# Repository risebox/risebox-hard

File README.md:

# risebox-hard
Hardware Plans &amp; Specifications

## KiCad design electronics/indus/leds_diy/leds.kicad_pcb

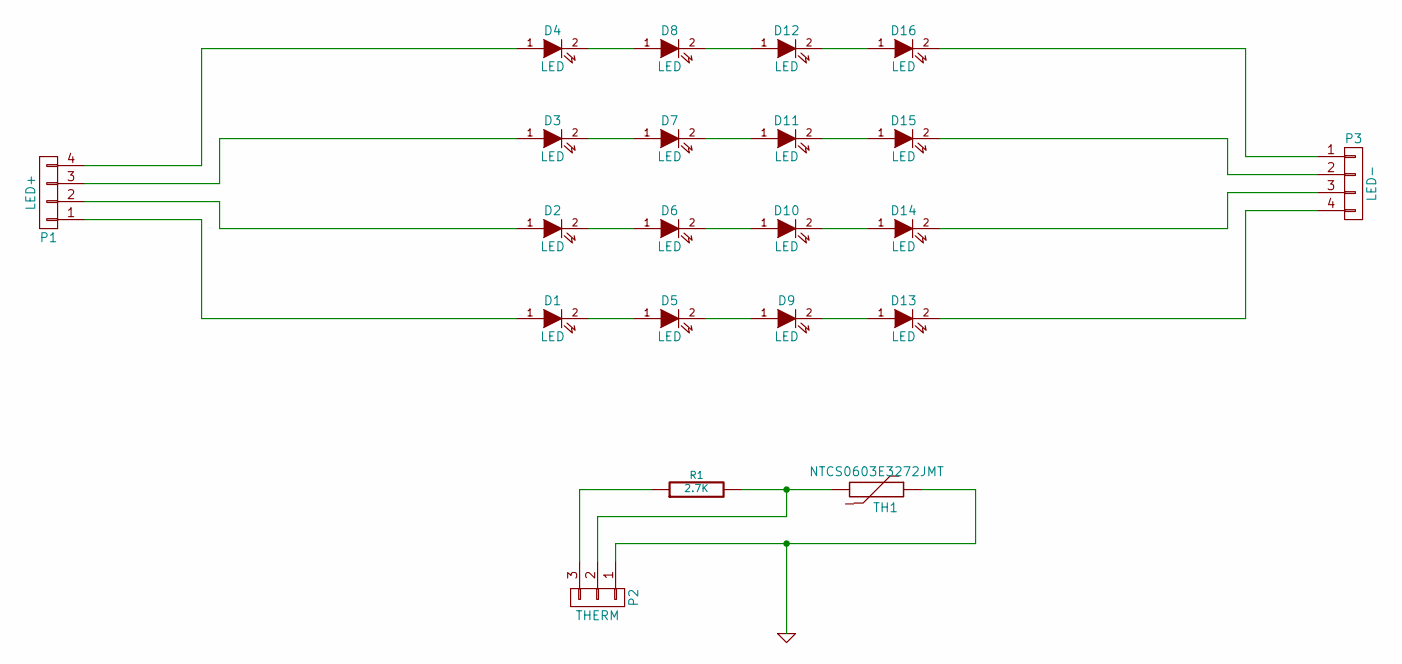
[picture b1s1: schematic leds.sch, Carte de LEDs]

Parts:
D1, D2, D3, D4, D5, D6, D7, D8, D9, D10, D11, D12, D13, D14, D15, D16: LED; LUXEON-C
P1: LED+; CONNECT_TE_3-647166-4
P2: THERM; CONNECT_TE_3-647166-3
P3: LED-; CONNECT_TE_3-647166-4
R1: 2.7K; R_0805
TH1: NTCS0603E3272JMT; THERM_NTCS0603E3272JMT_SMD0603

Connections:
GND: P2.1, TH1.1
unnamed: D1.1 (A), P1.1
unnamed: D1.2 (K), D5.1 (A)
unnamed: D2.1 (A), P1.2
unnamed: D2.2 (K), D6.1 (A)
unnamed: D3.1 (A), P1.3
unnamed: D3.2 (K), D7.1 (A)
unnamed: D4.1 (A), P1.4
unnamed: D4.2 (K), D8.1 (A)
unnamed: D5.2 (K), D9.1 (A)
unnamed: D6.2 (K), D10.1 (A)
unnamed: D10.2 (K), D14.1 (A)
unnamed: D7.2 (K), D11.1 (A)
unnamed: D11.2 (K), D15.1 (A)
unnamed: D8.2 (K), D12.1 (A)
unnamed: D12.2 (K), D16.1 (A)
unnamed: D9.2 (K), D13.1 (A)
unnamed: D13.2 (K), P3.4
unnamed: D14.2 (K), P3.3
unnamed: D15.2 (K), P3.2
unnamed: D16.2 (K), P3.1
unnamed: P2.2, R1.2, TH1.2
unnamed: P2.3, R1.1

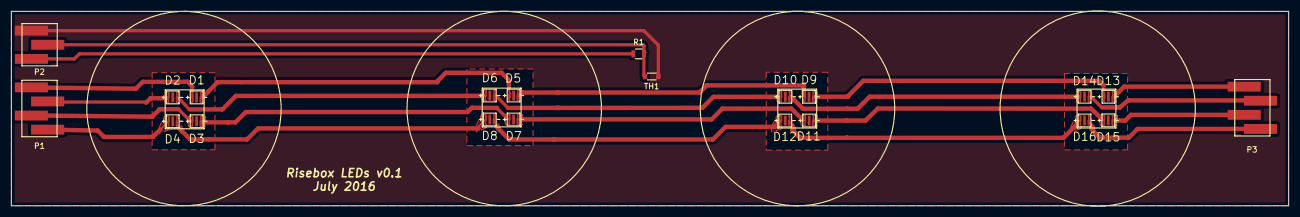
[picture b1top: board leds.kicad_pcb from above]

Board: 2 copper layers, 230.0 x 35.0 mm, 21 parts (0 on the bottom side), 23 nets.

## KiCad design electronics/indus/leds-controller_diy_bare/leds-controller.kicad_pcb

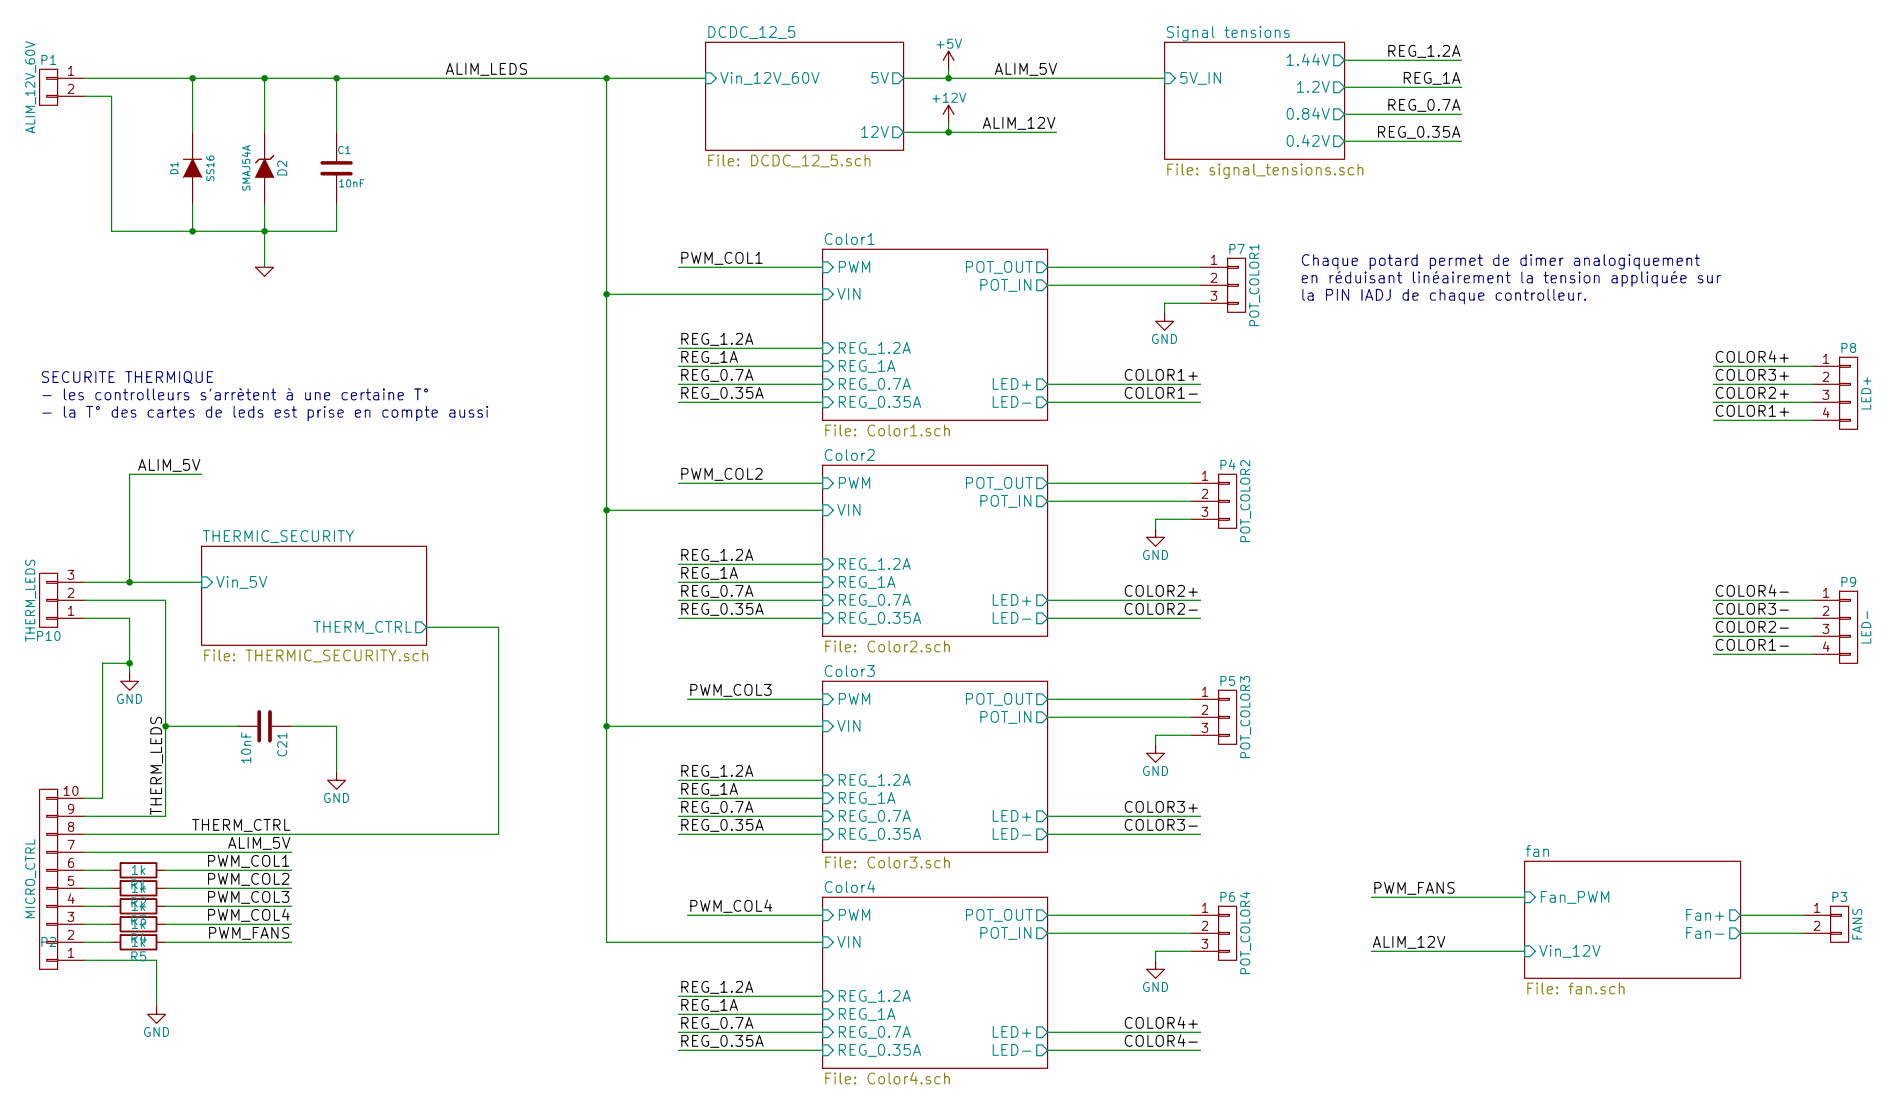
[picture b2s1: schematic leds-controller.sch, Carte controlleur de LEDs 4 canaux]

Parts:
C1, C21: 10nF; C_1206
D1: SS16; AB2_DO-214AC
D2: SMAJ54A; DIODE_DO_214_AA
P1: ALIM_12V_60V; TerminalBlock_Pheonix_MPT-2.54mm_2pol
P2: MICRO_CTRL; PINHEAD_LOCK_1-10
P3: FANS; PINHEAD_LOCK_1-2
P4: POT_COLOR2; POT_PTV09A-4020F-B103
P5: POT_COLOR3; POT_PTV09A-4020F-B103
P6: POT_COLOR4; POT_PTV09A-4020F-B103
P7: POT_COLOR1; POT_PTV09A-4020F-B103
P8: LED+; PINHEAD_LOCK_1-4
P9: LED-; PINHEAD_LOCK_1-4
P10: THERM_LEDS; PINHEAD_LOCK_1-3
R1, R2, R3, R4, R5: 1k; R_0805

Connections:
+5V: P2.7, P10.3; also elsewhere on the board
+12V: P3.1; also elsewhere on the board
/Color1/LED+: P8.4; also elsewhere on the board
/Color1/LED-: P9.4; also elsewhere on the board
/Color1/POT_IN: P7.2; also elsewhere on the board
/Color1/POT_OUT: P7.1; also elsewhere on the board
/Color1/PWM: R1.1; also elsewhere on the board
/Color1/VIN: C1.1, D1.2 (K), D2.2 (K), P1.1; also elsewhere on the board
/Color2/LED+: P8.3; also elsewhere on the board
/Color2/LED-: P9.3; also elsewhere on the board
/Color2/POT_IN: P4.2; also elsewhere on the board
/Color2/POT_OUT: P4.1; also elsewhere on the board
/Color2/PWM: R2.1; also elsewhere on the board
/Color3/LED+: P8.2; also elsewhere on the board
/Color3/LED-: P9.2; also elsewhere on the board
/Color3/POT_IN: P5.2; also elsewhere on the board
/Color3/POT_OUT: P5.1; also elsewhere on the board
/Color3/PWM: R3.1; also elsewhere on the board
/Color4/LED+: P8.1; also elsewhere on the board
/Color4/LED-: P9.1; also elsewhere on the board
/Color4/POT_IN: P6.2; also elsewhere on the board
/Color4/POT_OUT: P6.1; also elsewhere on the board
/Color4/PWM: R4.1; also elsewhere on the board
/THERMIC_SECURITY/THERM_CTRL: P2.8; also elsewhere on the board
/THERM_LEDS: C21.2, P2.9, P10.2
/fan/Fan-: P3.2; also elsewhere on the board
/fan/Fan_PWM: R5.1; also elsewhere on the board
GND: C1.2, C21.1, D1.1 (A), D2.1 (A), P1.2, P2.1, P2.10, P4.3, P5.3, P6.3, P7.3, P10.1; also elsewhere on the board
unnamed: P2.2, R5.2
unnamed: P2.3, R4.2
unnamed: P2.4, R3.2
unnamed: P2.5, R2.2
unnamed: P2.6, R1.2

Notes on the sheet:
Chaque potard permet de dimer analogiquement en réduisant linéairement la tension appliquée sur la PIN IADJ de chaque controlleur.
SECURITE THERMIQUE - les controlleurs s'arrètent à une certaine T° - la T° des cartes de leds est prise en compte aussi

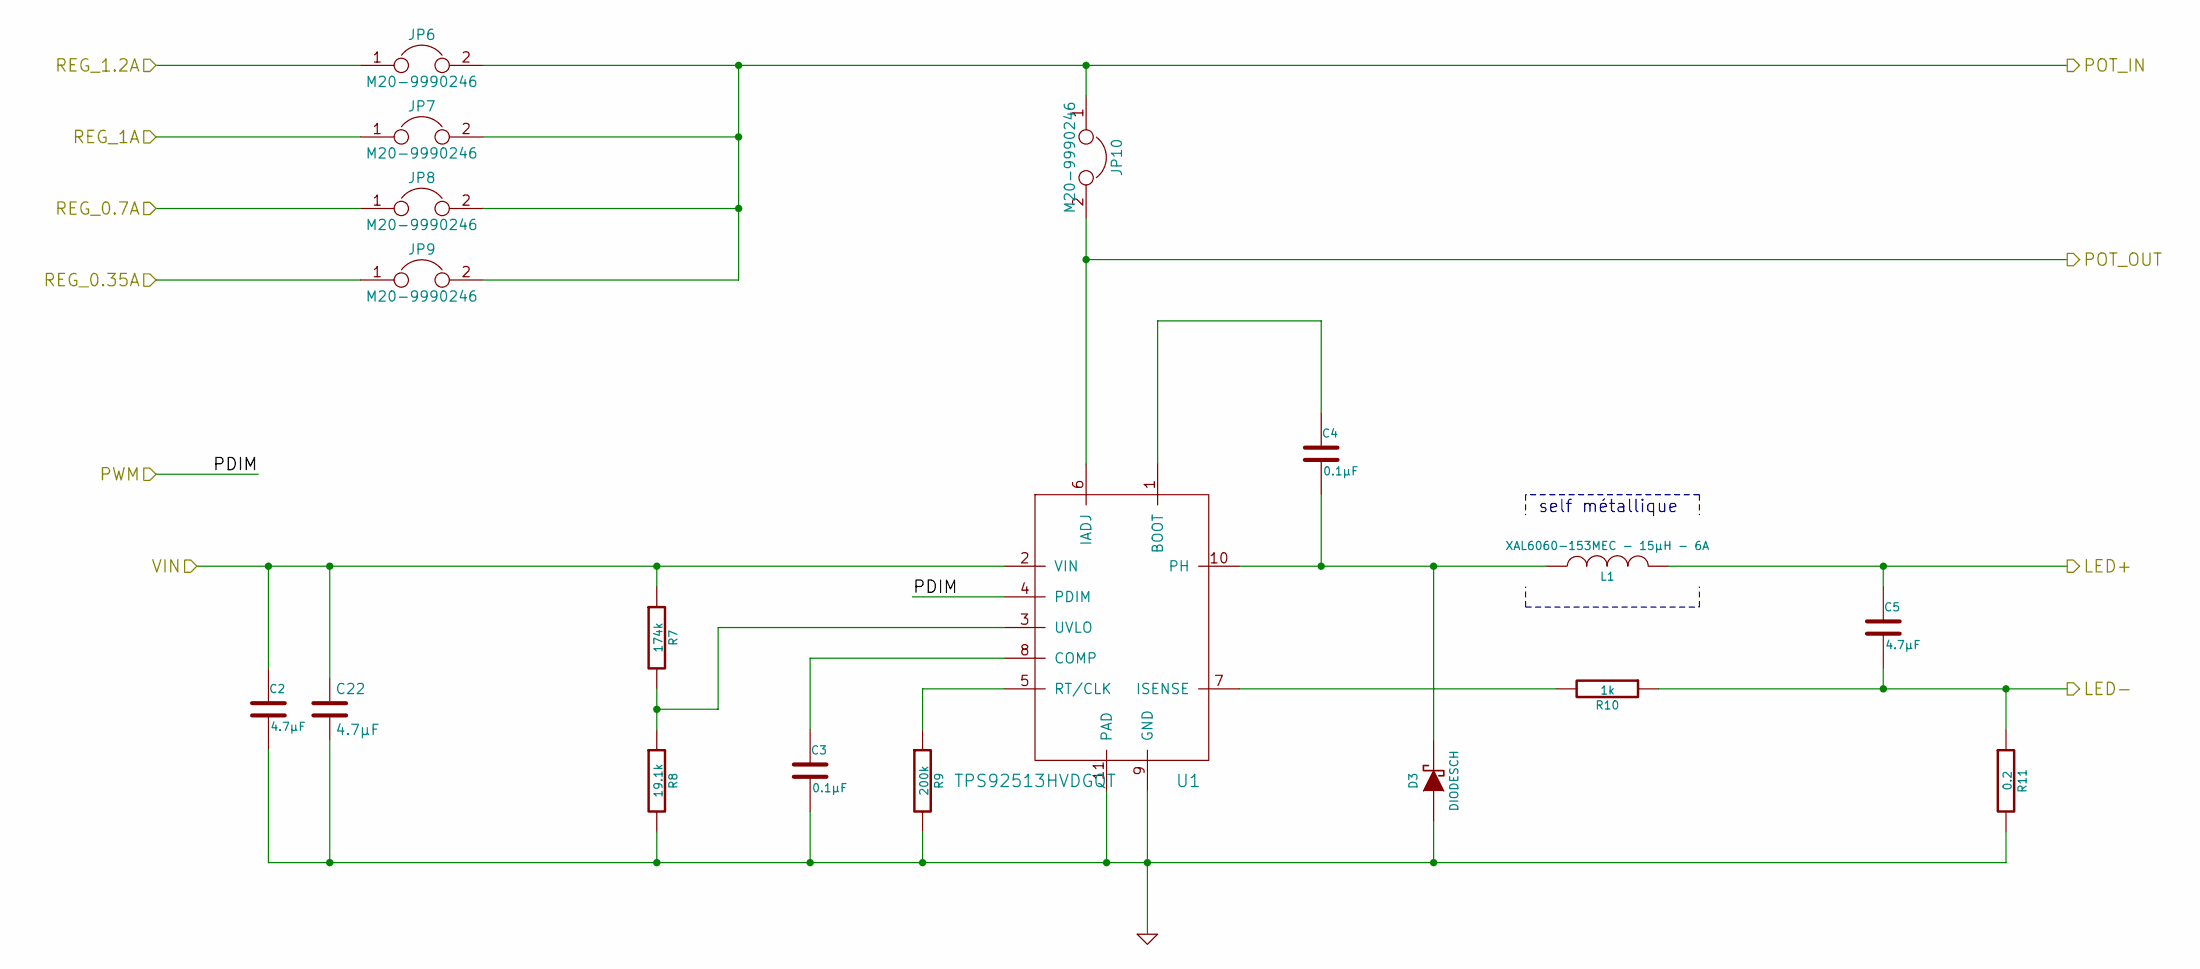
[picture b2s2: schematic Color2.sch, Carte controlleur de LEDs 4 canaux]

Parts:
C2, C5, C22: 4.7µF; C_1206
C3, C4: 0.1µF; C_0805
D3: DIODESCH; SOD-123
JP6, JP7, JP8, JP9, JP10: M20-9990246; PINHEAD1-2
L1: XAL6060-153MEC - 15µH - 6A; SELF_COILCRAFT_XAL6060-153
R7: 174k; R_0805
R8: 19.1k; R_0805
R9: 200k; R_0805
R10: 1k; R_0805
R11: 0.2; R_1206
U1: TPS92513HVDGQT; BUCK_TPS92513_PowerPAD

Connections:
/Color1/VIN: C2.1, C22.1, R7.1, U1.2 (VIN); also elsewhere on the board
/Color2/LED+: C5.1, L1.2; also elsewhere on the board
/Color2/LED-: C5.2, R10.1, R11.1; also elsewhere on the board
/Color2/POT_IN: JP6.2, JP7.2, JP8.2, JP9.2, JP10.1; also elsewhere on the board
/Color2/POT_OUT: JP10.2, U1.6 (IADJ); also elsewhere on the board
/Color2/PWM: U1.4 (PDIM); also elsewhere on the board
/Signal tensions/0.42V: JP9.1; also elsewhere on the board
/Signal tensions/0.84V: JP8.1; also elsewhere on the board
/Signal tensions/1.2V: JP7.1; also elsewhere on the board
/Signal tensions/1.44V: JP6.1; also elsewhere on the board
GND: C2.2, C3.2, C22.2, D3.1 (A), R8.2, R9.2, R11.2, U1.9 (GND), U1.11 (PAD); also elsewhere on the board
unnamed: C3.1, U1.8 (COMP)
unnamed: C4.1, U1.1 (BOOT)
unnamed: C4.2, D3.2 (K), L1.1, U1.10 (PH)
unnamed: R7.2, R8.1, U1.3 (UVLO)
unnamed: R9.1, U1.5 (RT/CLK)
unnamed: R10.2, U1.7 (ISENSE)

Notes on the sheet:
self métallique

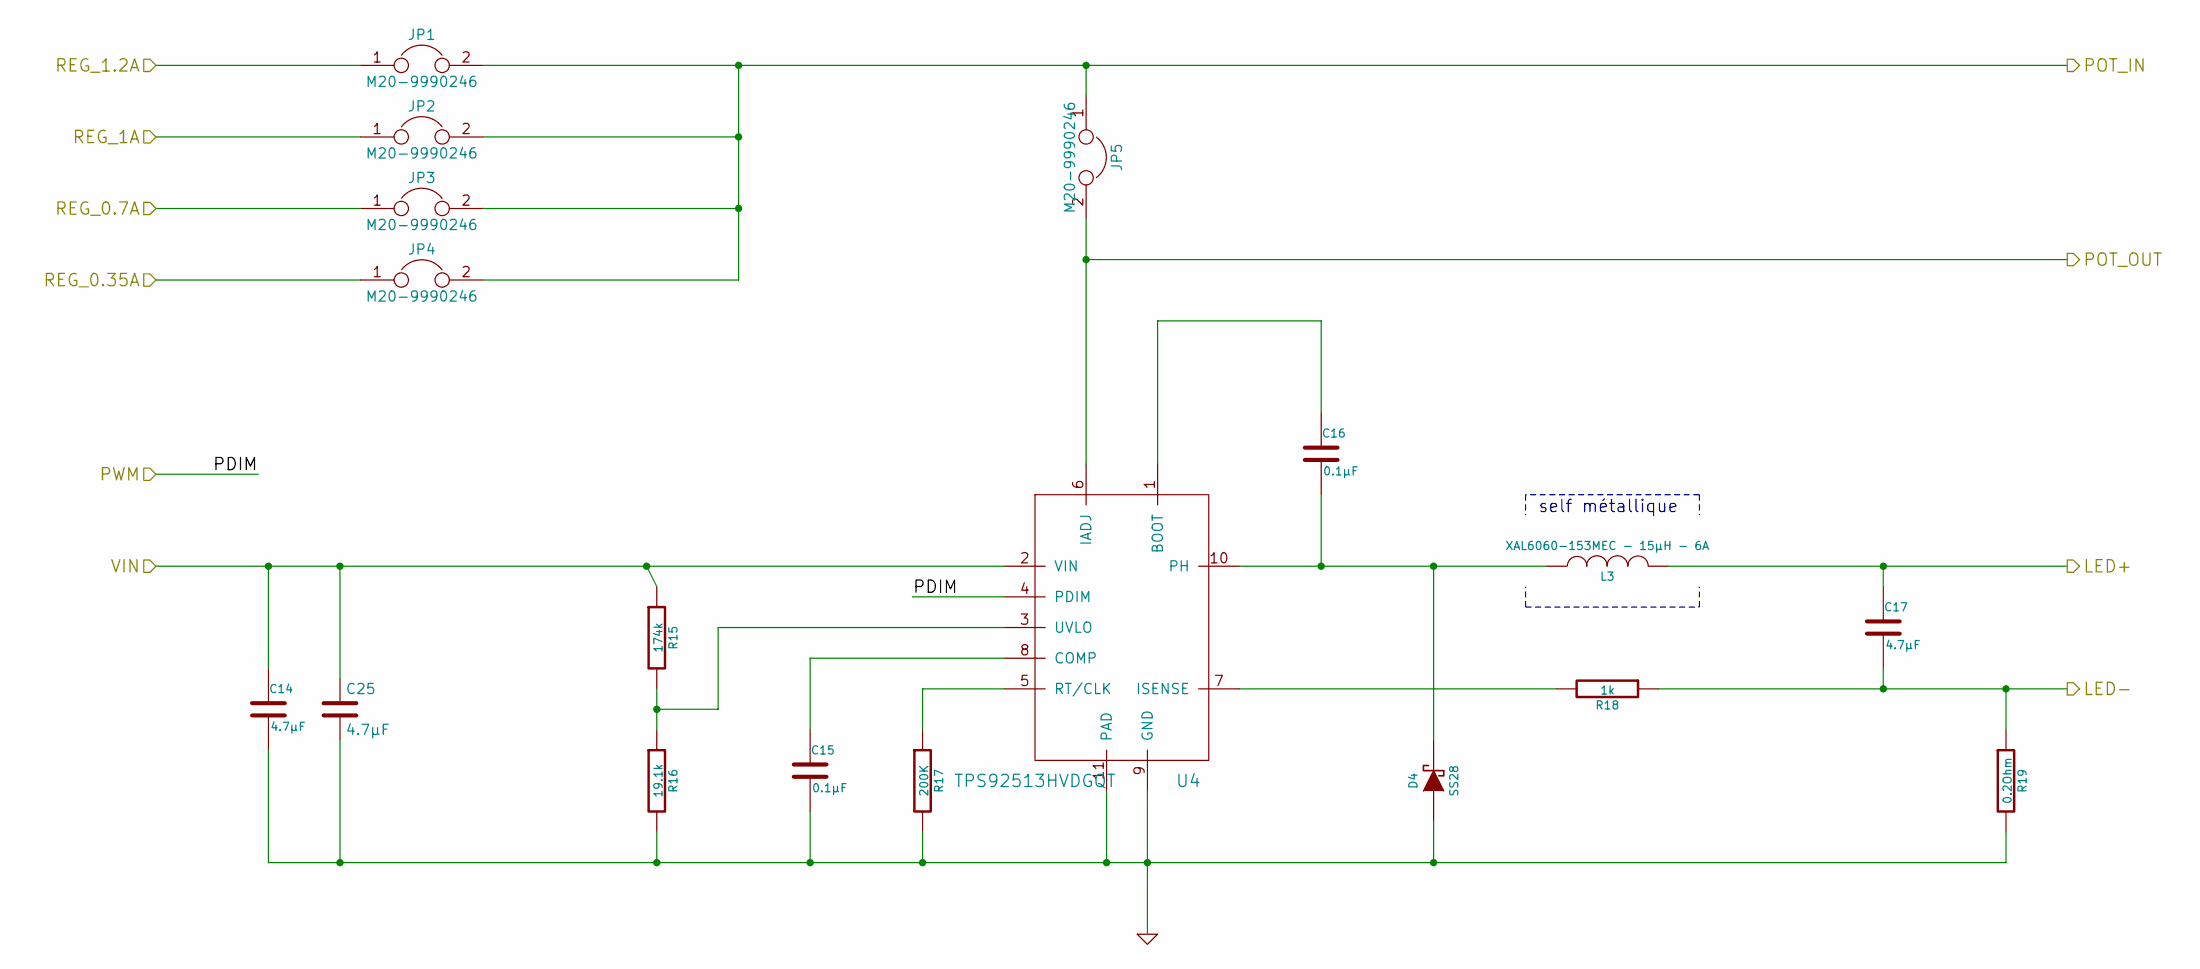
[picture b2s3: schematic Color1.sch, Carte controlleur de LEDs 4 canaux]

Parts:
C14, C17, C25: 4.7µF; C_1206
C15, C16: 0.1µF; C_0805
D4: SS28; SOD-123
JP1, JP2, JP3, JP4, JP5: M20-9990246; PINHEAD1-2
L3: XAL6060-153MEC - 15µH - 6A; SELF_COILCRAFT_XAL6060-153
R15: 174k; R_0805
R16: 19.1k; R_0805
R17: 200K; R_0805
R18: 1k; R_0805
R19: 0.2Ohm; R_1206
U4: TPS92513HVDGQT; BUCK_TPS92513_PowerPAD

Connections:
/Color1/LED+: C17.1, L3.2; also elsewhere on the board
/Color1/LED-: C17.2, R18.1, R19.1; also elsewhere on the board
/Color1/POT_IN: JP1.2, JP2.2, JP3.2, JP4.2, JP5.1; also elsewhere on the board
/Color1/POT_OUT: JP5.2, U4.6 (IADJ); also elsewhere on the board
/Color1/PWM: U4.4 (PDIM); also elsewhere on the board
/Color1/VIN: C14.1, C25.1, R15.1, U4.2 (VIN); also elsewhere on the board
/Signal tensions/0.42V: JP4.1; also elsewhere on the board
/Signal tensions/0.84V: JP3.1; also elsewhere on the board
/Signal tensions/1.2V: JP2.1; also elsewhere on the board
/Signal tensions/1.44V: JP1.1; also elsewhere on the board
GND: C14.2, C15.2, C25.2, D4.1 (A), R16.2, R17.2, R19.2, U4.9 (GND), U4.11 (PAD); also elsewhere on the board
unnamed: C15.1, U4.8 (COMP)
unnamed: C16.1, U4.1 (BOOT)
unnamed: C16.2, D4.2 (K), L3.1, U4.10 (PH)
unnamed: R15.2, R16.1, U4.3 (UVLO)
unnamed: R17.1, U4.5 (RT/CLK)
unnamed: R18.2, U4.7 (ISENSE)

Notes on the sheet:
self métallique

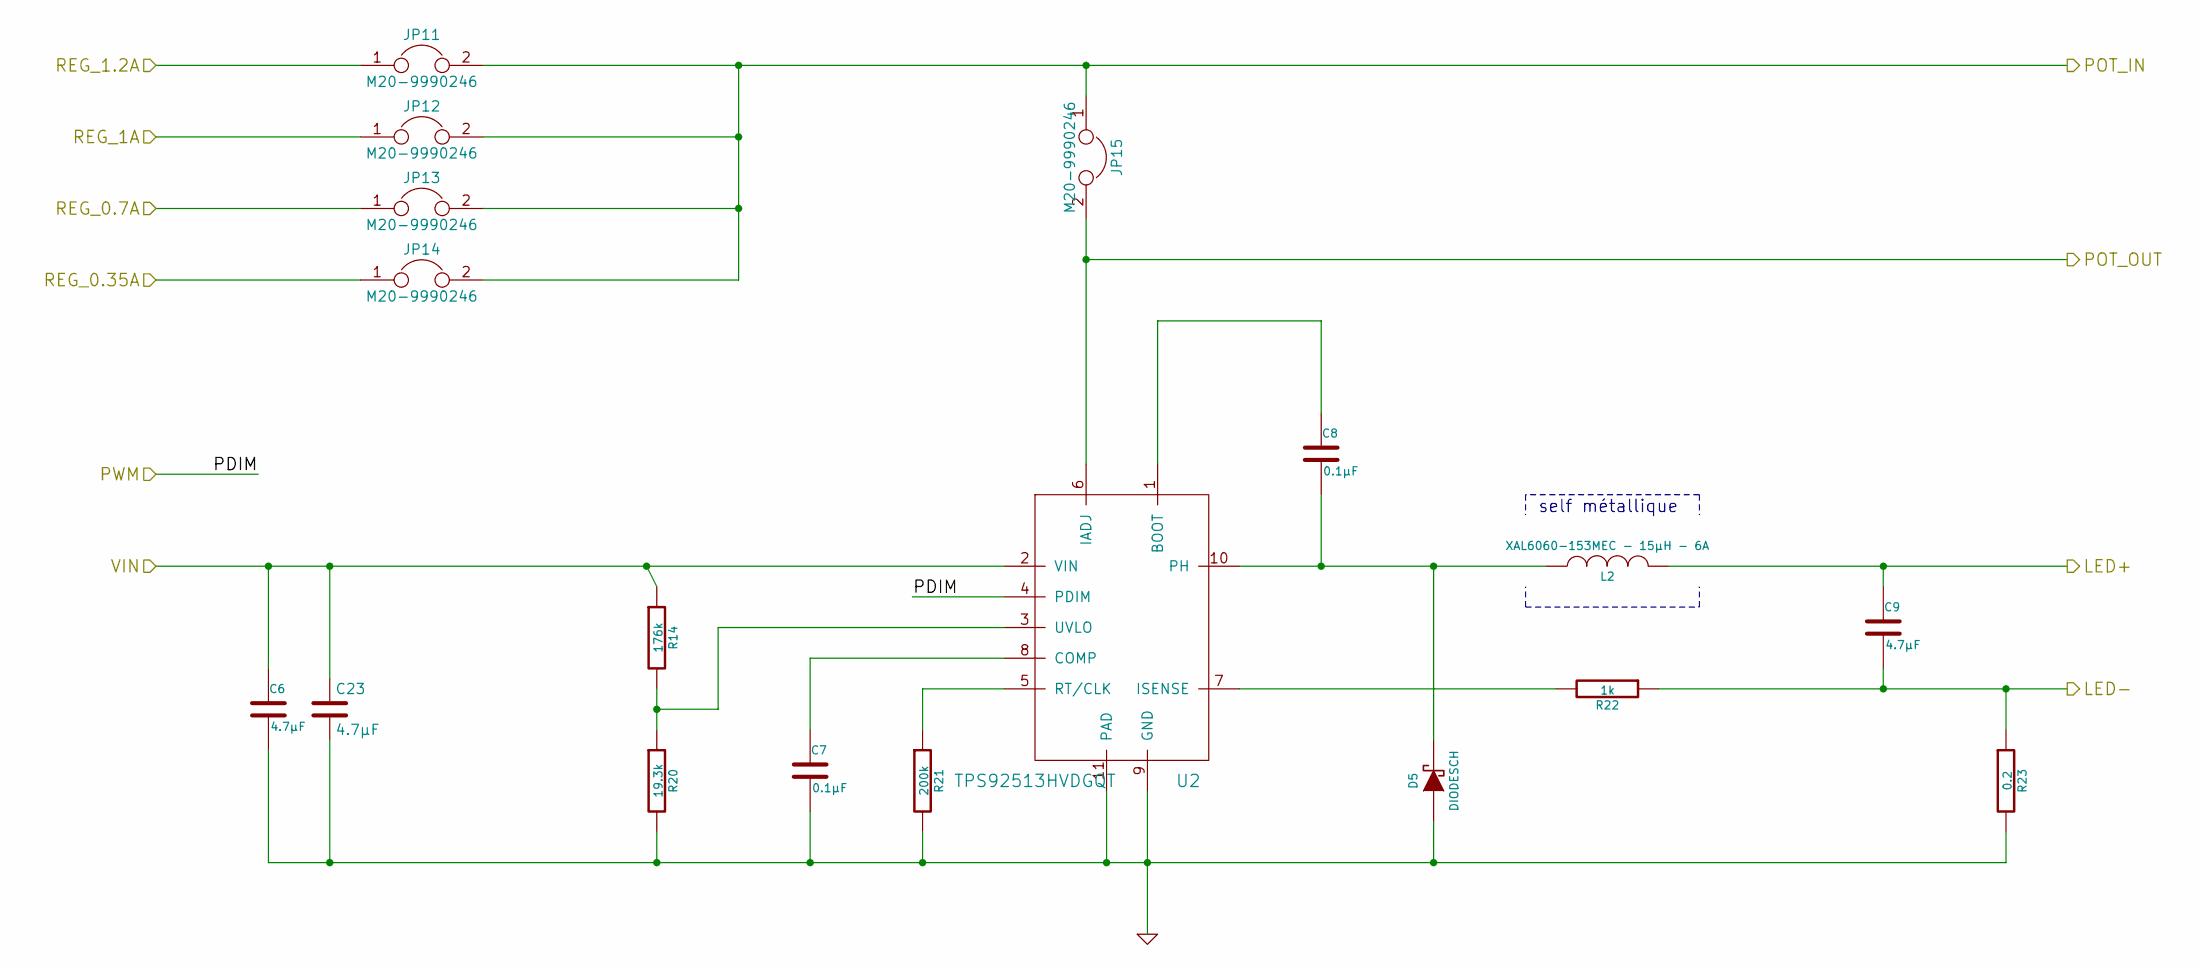
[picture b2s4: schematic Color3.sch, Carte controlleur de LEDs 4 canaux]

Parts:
C6, C9, C23: 4.7µF; C_1206
C7, C8: 0.1µF; C_0805
D5: DIODESCH; SOD-123
JP11, JP12, JP13, JP14, JP15: M20-9990246; PINHEAD1-2
L2: XAL6060-153MEC - 15µH - 6A; SELF_COILCRAFT_XAL6060-153
R14: 176k; R_0805
R20: 19.3k; R_0805
R21: 200k; R_0805
R22: 1k; R_0805
R23: 0.2; R_1206
U2: TPS92513HVDGQT; BUCK_TPS92513_PowerPAD

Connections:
/Color1/VIN: C6.1, C23.1, R14.1, U2.2 (VIN); also elsewhere on the board
/Color3/LED+: C9.1, L2.2; also elsewhere on the board
/Color3/LED-: C9.2, R22.1, R23.1; also elsewhere on the board
/Color3/POT_IN: JP11.2, JP12.2, JP13.2, JP14.2, JP15.1; also elsewhere on the board
/Color3/POT_OUT: JP15.2, U2.6 (IADJ); also elsewhere on the board
/Color3/PWM: U2.4 (PDIM); also elsewhere on the board
/Signal tensions/0.42V: JP14.1; also elsewhere on the board
/Signal tensions/0.84V: JP13.1; also elsewhere on the board
/Signal tensions/1.2V: JP12.1; also elsewhere on the board
/Signal tensions/1.44V: JP11.1; also elsewhere on the board
GND: C6.2, C7.2, C23.2, D5.1 (A), R20.2, R21.2, R23.2, U2.9 (GND), U2.11 (PAD); also elsewhere on the board
unnamed: C7.1, U2.8 (COMP)
unnamed: C8.1, U2.1 (BOOT)
unnamed: C8.2, D5.2 (K), L2.1, U2.10 (PH)
unnamed: R14.2, R20.1, U2.3 (UVLO)
unnamed: R21.1, U2.5 (RT/CLK)
unnamed: R22.2, U2.7 (ISENSE)

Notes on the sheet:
self métallique

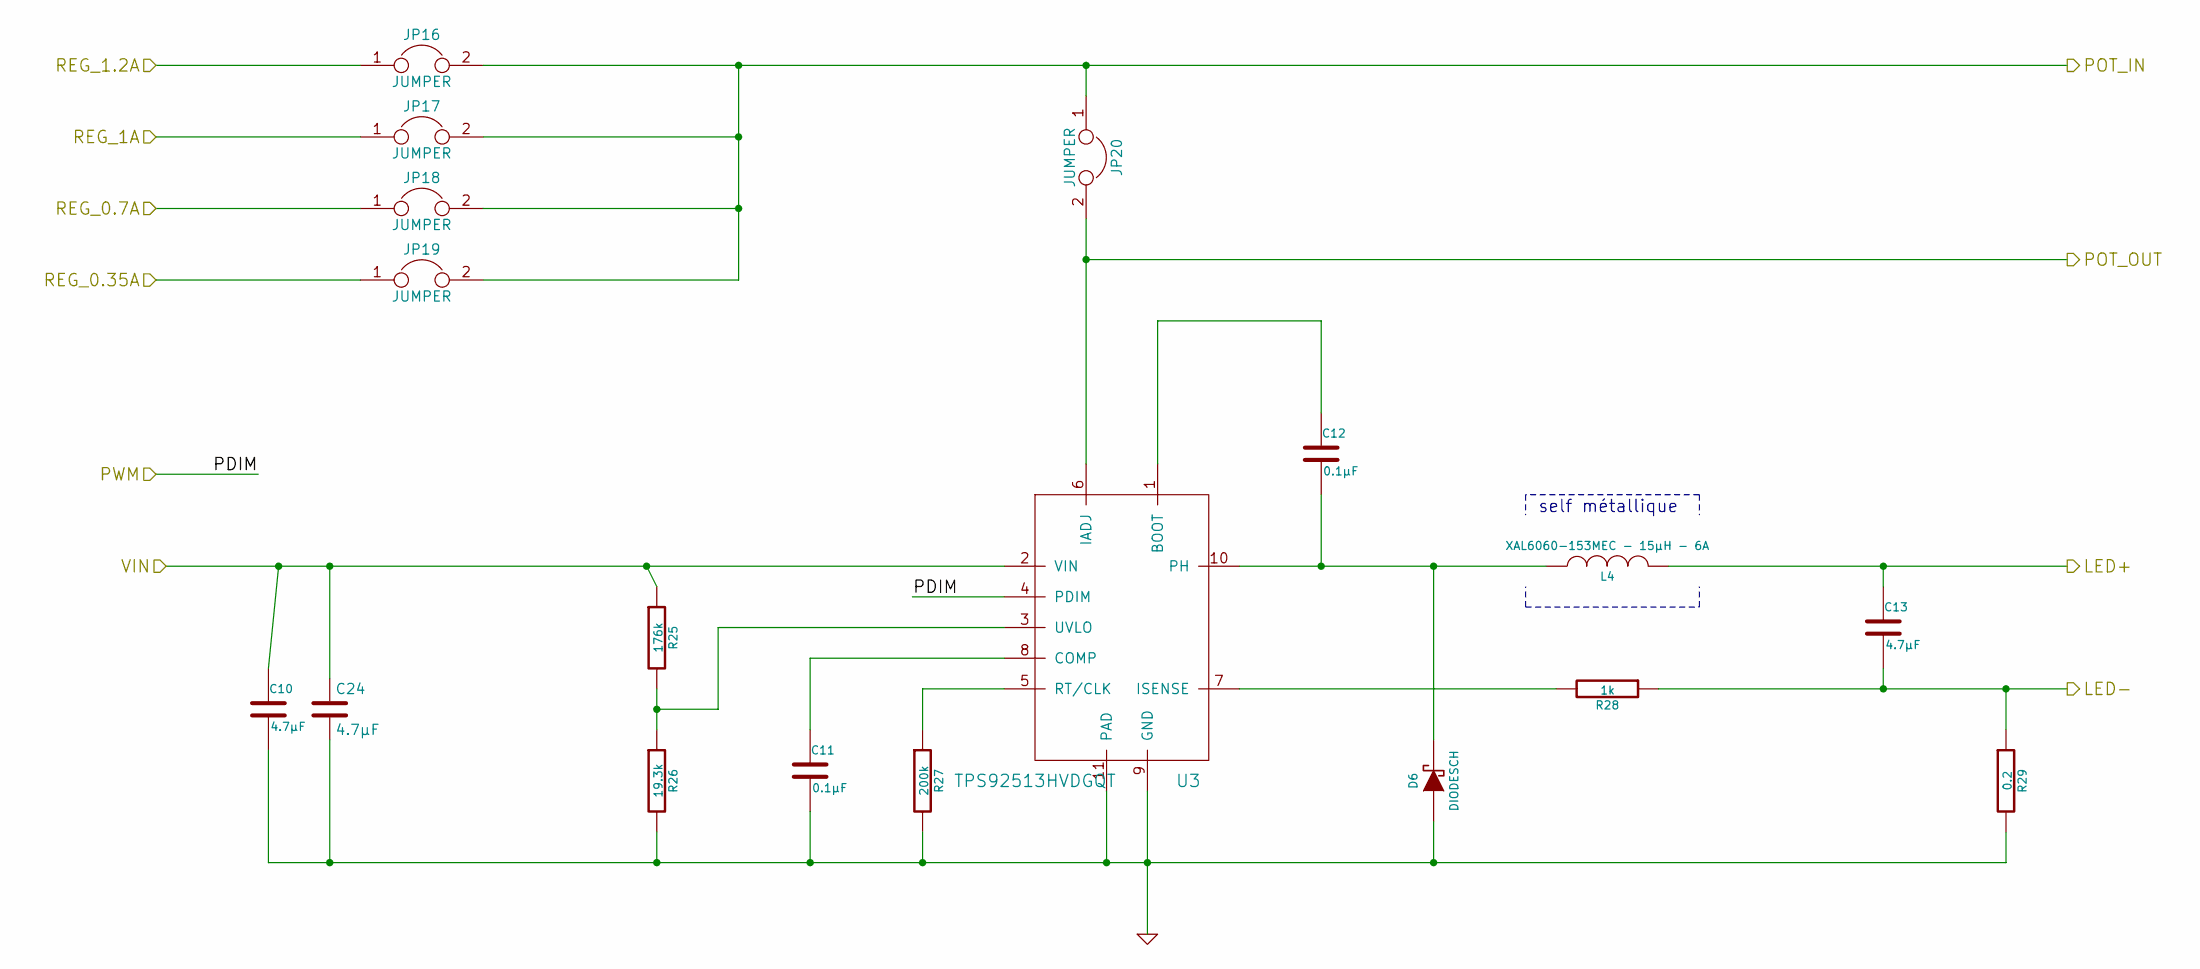
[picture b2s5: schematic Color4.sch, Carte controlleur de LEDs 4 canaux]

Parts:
C10, C13, C24: 4.7µF; C_1206
C11, C12: 0.1µF; C_0805
D6: DIODESCH; SOD-123
JP16, JP17, JP18, JP19, JP20: JUMPER
L4: XAL6060-153MEC - 15µH - 6A; SELF_COILCRAFT_XAL6060-153
R25: 176k; R_0805
R26: 19.3k; R_0805
R27: 200k; R_0805
R28: 1k; R_0805
R29: 0.2; R_1206
U3: TPS92513HVDGQT; BUCK_TPS92513_PowerPAD

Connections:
/Color1/VIN: C10.1, C24.1, R25.1, U3.2 (VIN); also elsewhere on the board
/Color4/LED+: C13.1, L4.2; also elsewhere on the board
/Color4/LED-: C13.2, R28.1, R29.1; also elsewhere on the board
/Color4/POT_IN: JP16.2, JP17.2, JP18.2, JP19.2, JP20.1; also elsewhere on the board
/Color4/POT_OUT: JP20.2, U3.6 (IADJ); also elsewhere on the board
/Color4/PWM: U3.4 (PDIM); also elsewhere on the board
/Signal tensions/0.42V: JP19.1; also elsewhere on the board
/Signal tensions/0.84V: JP18.1; also elsewhere on the board
/Signal tensions/1.2V: JP17.1; also elsewhere on the board
/Signal tensions/1.44V: JP16.1; also elsewhere on the board
GND: C10.2, C11.2, C24.2, D6.1 (A), R26.2, R27.2, R29.2, U3.9 (GND), U3.11 (PAD); also elsewhere on the board
unnamed: C11.1, U3.8 (COMP)
unnamed: C12.1, U3.1 (BOOT)
unnamed: C12.2, D6.2 (K), L4.1, U3.10 (PH)
unnamed: R25.2, R26.1, U3.3 (UVLO)
unnamed: R27.1, U3.5 (RT/CLK)
unnamed: R28.2, U3.7 (ISENSE)

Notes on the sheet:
self métallique

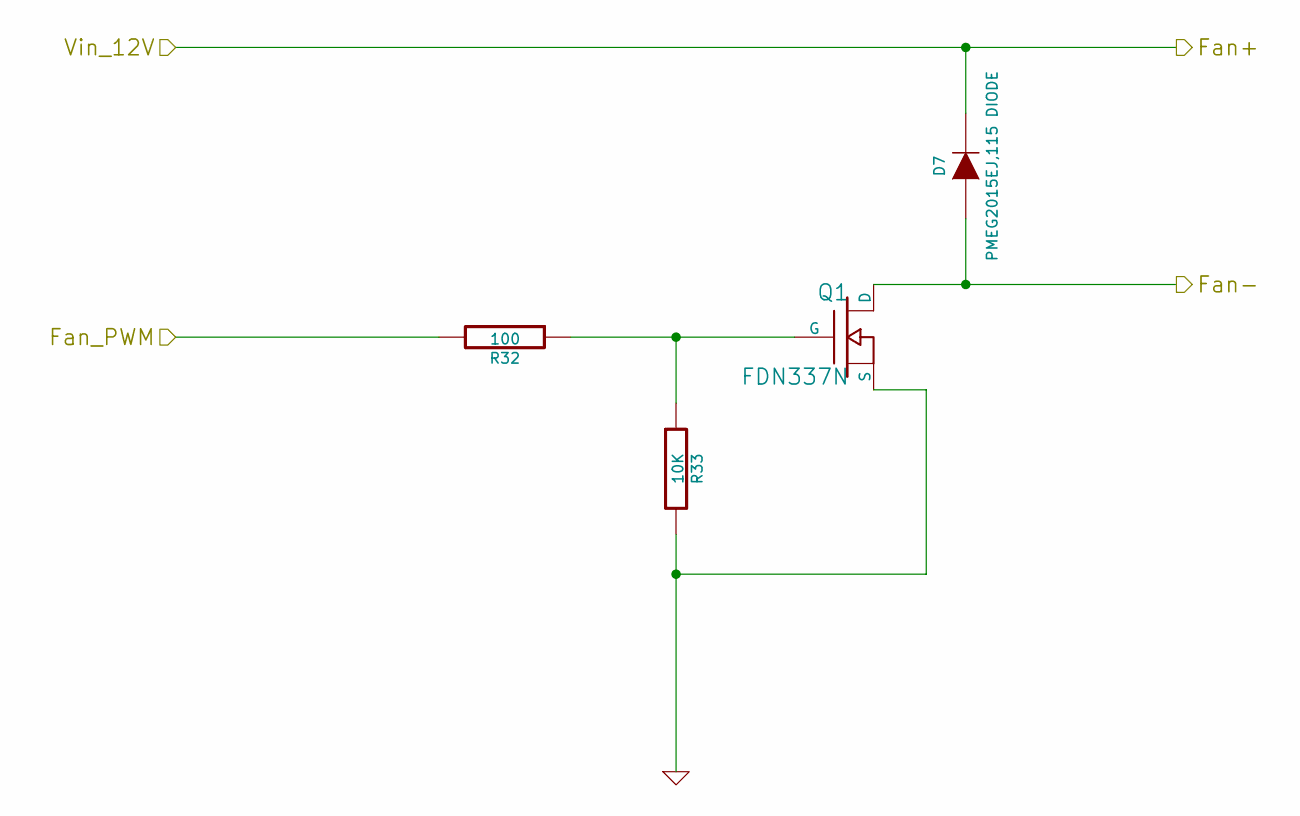
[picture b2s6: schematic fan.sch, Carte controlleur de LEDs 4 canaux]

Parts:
D7: PMEG2015EJ,115 DIODE; AB2_DO-214AC
Q1: FDN337N; SOT-23-FET
R32: 100; R_0603
R33: 10K; R_0603

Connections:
+12V: D7.2 (K); also elsewhere on the board
/fan/Fan-: D7.1 (A), Q1.D; also elsewhere on the board
/fan/Fan_PWM: R32.2; also elsewhere on the board
GND: Q1.S, R33.2; also elsewhere on the board
unnamed: Q1.G, R32.1, R33.1

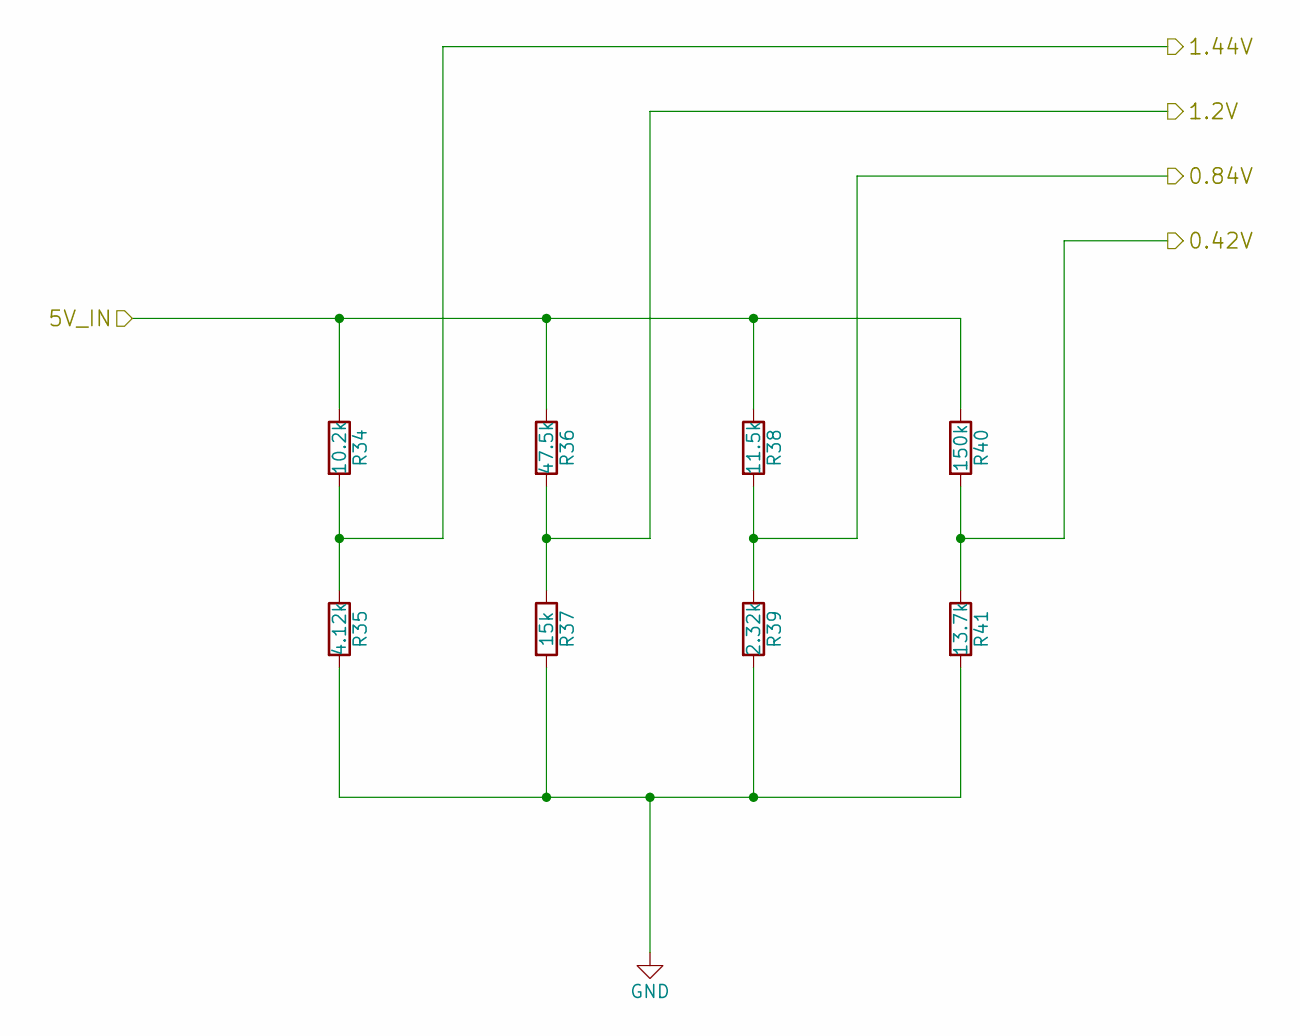
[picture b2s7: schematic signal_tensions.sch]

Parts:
R34: 10.2k; R_0805
R35: 4.12k; R_0805
R36: 47.5k; R_0805
R37: 15k; R_0805
R38: 11.5k; R_0805
R39: 2.32k; R_0805
R40: 150k; R_0805
R41: 13.7k; R_0805

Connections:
+5V: R34.1, R36.1, R38.1, R40.1; also elsewhere on the board
/Signal tensions/0.42V: R40.2, R41.1; also elsewhere on the board
/Signal tensions/0.84V: R38.2, R39.1; also elsewhere on the board
/Signal tensions/1.2V: R36.2, R37.1; also elsewhere on the board
/Signal tensions/1.44V: R34.2, R35.1; also elsewhere on the board
GND: R35.2, R37.2, R39.2, R41.2; also elsewhere on the board

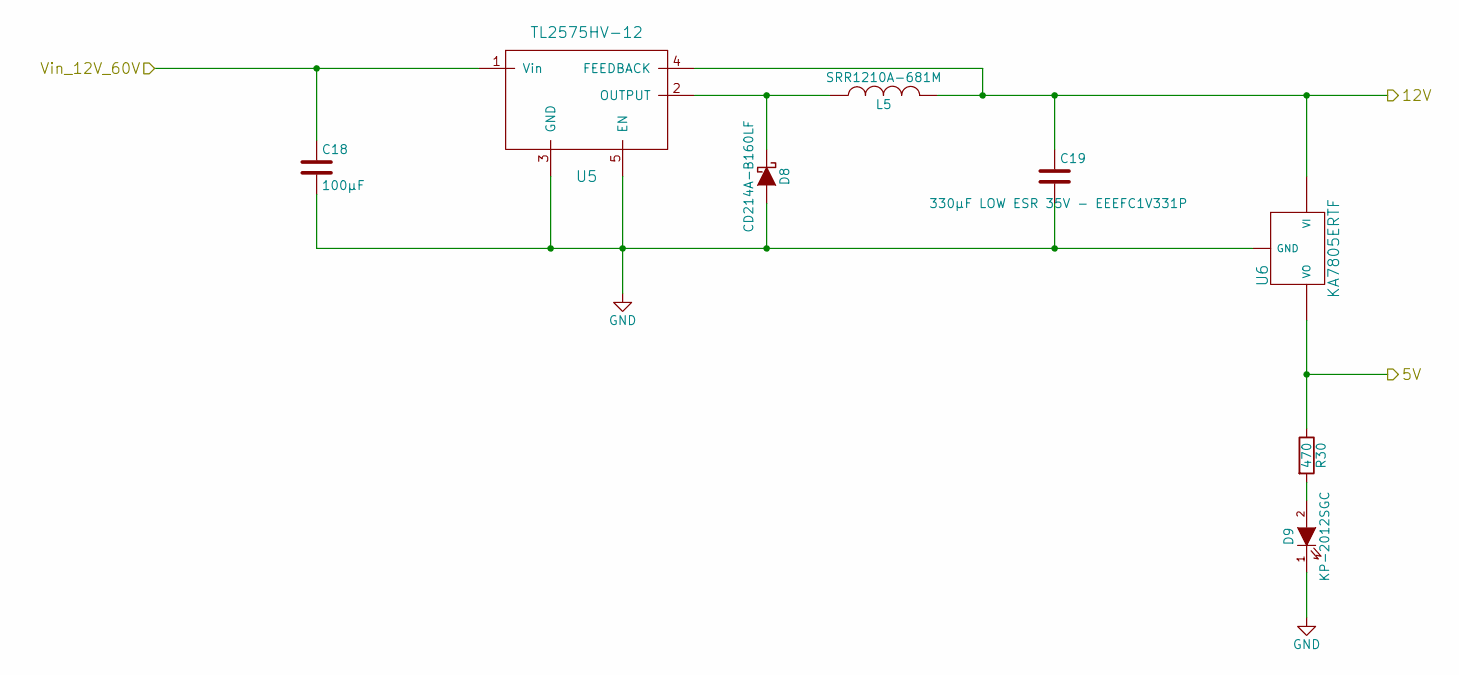
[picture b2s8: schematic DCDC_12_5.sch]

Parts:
C18: 100µF; C_Radial_D10_L20_P5
C19: 330µF LOW ESR 35V - EEEFC1V331P; CAPA_EEEFC1V331P
D8: CD214A-B160LF; AB2_DO-214AC
D9: KP-2012SGC; LED-KPH-2012SGC
L5: SRR1210A-681M; INDUC_SRR1210A
R30: 470; R_0805
U5: TL2575HV-12; TO-263-5Lead
U6: KA7805ERTF; KA7805ERTF_TO-252-3

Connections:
+5V: R30.1, U6.VO; also elsewhere on the board
+12V: C19.1, L5.2, U5.4 (FEEDBACK), U6.VI; also elsewhere on the board
/Color1/VIN: C18.1, U5.1 (Vin); also elsewhere on the board
GND: C18.2, C19.2, D8.2 (A), D9.1 (K), U5.3 (GND), U5.5 (EN), U6.GND; also elsewhere on the board
unnamed: D8.1 (K), L5.1, U5.2 (OUTPUT)
unnamed: D9.2 (A), R30.2

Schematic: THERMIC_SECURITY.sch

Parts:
C20: 10nF; C_1206
R42: 2.55K; R_0805
TH1: NTCS0805E3103JMT; THERM_NTCS0603E3272JMT_SMD0603

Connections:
+5V: TH1.1; also elsewhere on the board
/THERMIC_SECURITY/THERM_CTRL: C20.1, R42.1, TH1.2; also elsewhere on the board
GND: C20.2, R42.2; also elsewhere on the board

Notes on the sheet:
1V à 25°, 4V à 115°

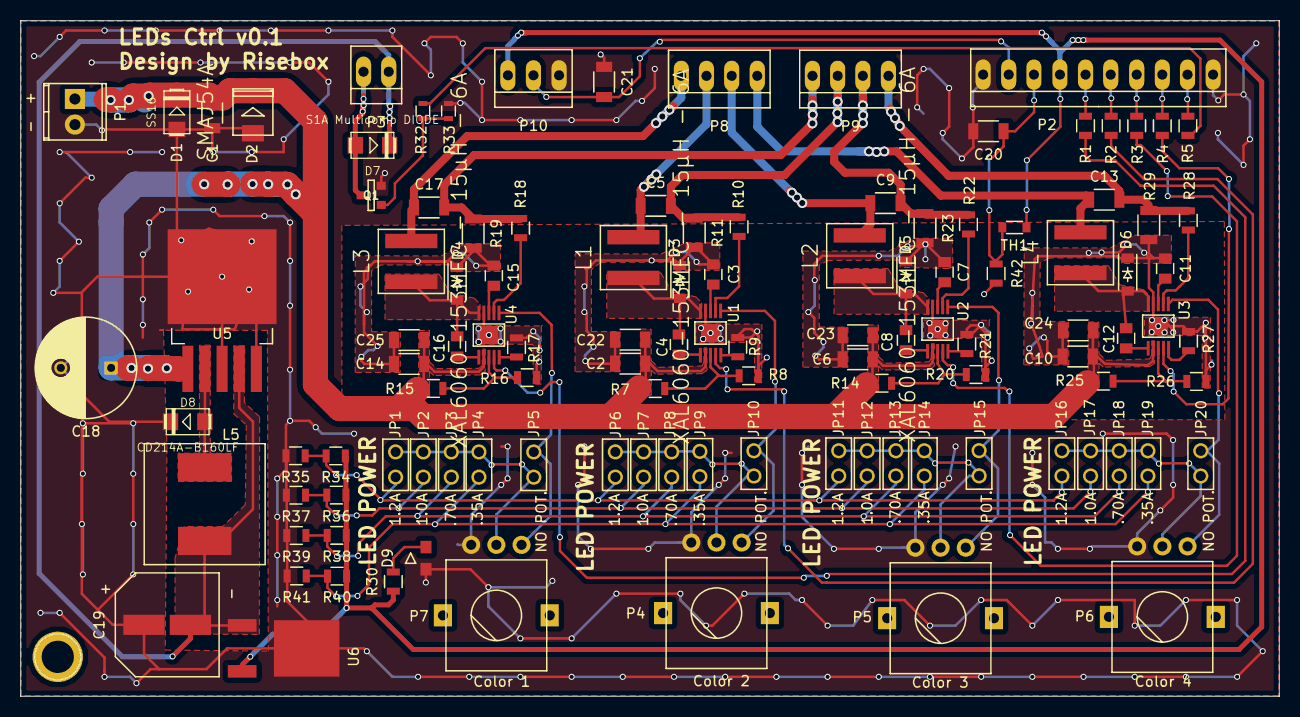
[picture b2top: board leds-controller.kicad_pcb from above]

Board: 2 copper layers, 124.9 x 67.0 mm, 114 parts (0 on the bottom side), 64 nets.
